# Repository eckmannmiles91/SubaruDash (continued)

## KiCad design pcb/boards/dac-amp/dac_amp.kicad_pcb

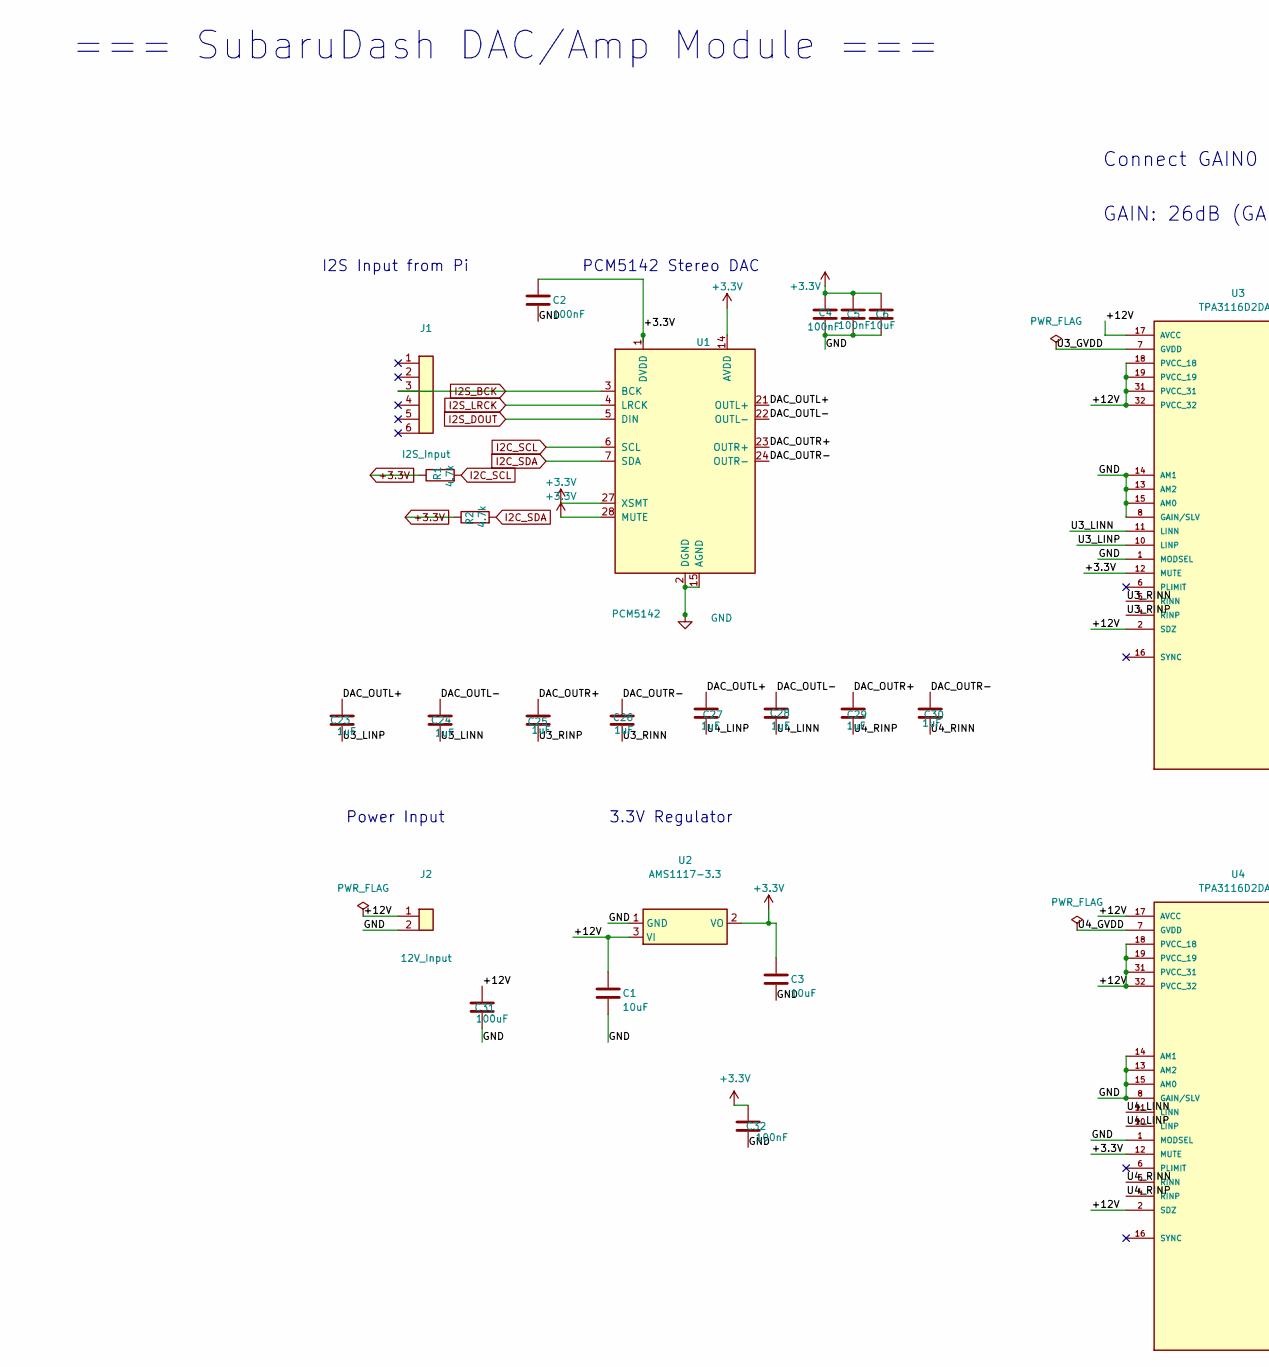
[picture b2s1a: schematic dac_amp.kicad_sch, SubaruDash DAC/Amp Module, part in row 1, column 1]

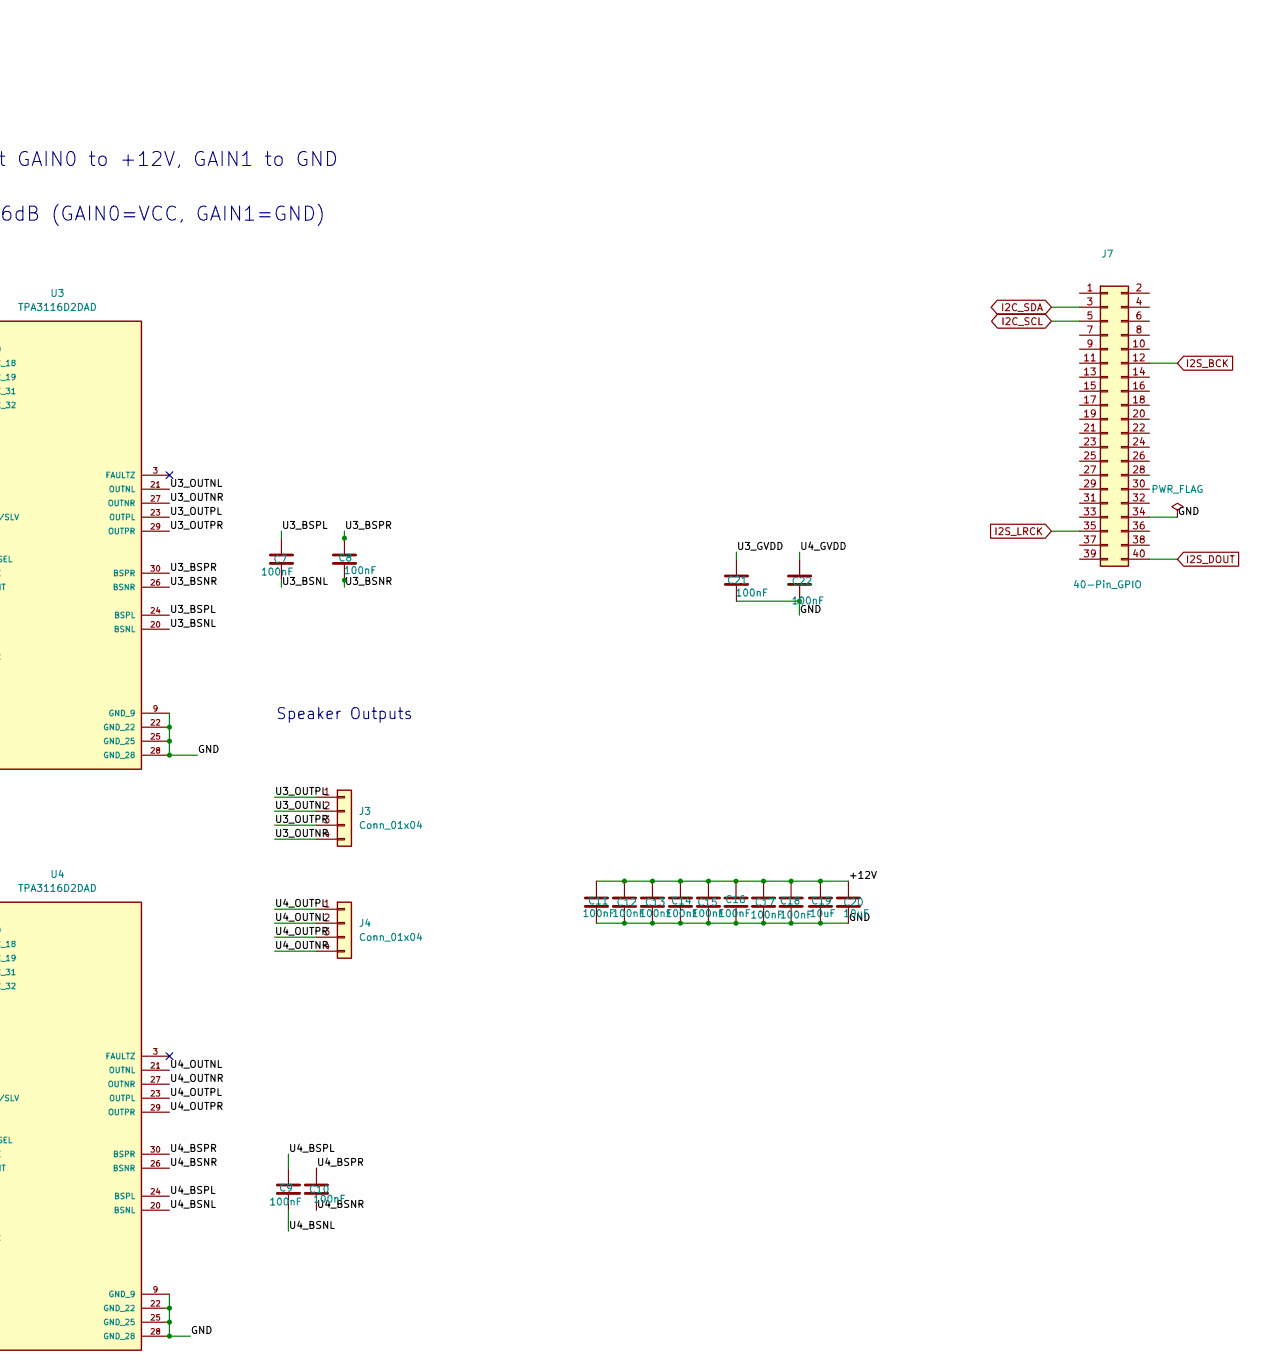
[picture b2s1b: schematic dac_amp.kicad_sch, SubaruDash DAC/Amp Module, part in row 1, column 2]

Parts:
C1, C3, C6: 10uF; C_0805_2012Metric
C2, C4, C5, C7, C8, C9, C10, C11, C12, C13, C14, C15, C16, C17, C18, C21, C22, C32: 100nF; C_0805_2012Metric
C19, C20: 10uF; C_1206_3216Metric
C23, C24, C25, C26, C27, C28, C29, C30: 1uF; C_0805_2012Metric
C31: 100uF; CP_Radial_D8.0mm_P3.50mm
J1: I2S_Input; PinHeader_1x06_P2.54mm_Vertical
J2: 12V_Input; PhoenixContact_MSTBA_2,5_2-G-5,08_1x02_P5.08mm_Horizontal
J3, J4: Conn_01x04; TerminalBlock_Phoenix_PT-1,5-4-3.5-H_1x04_P3.50mm_Horizontal
J7: 40-Pin_GPIO; PinSocket_2x20_P2.54mm_Vertical
R1, R2: 4.7k; R_0805_2012Metric
U1: PCM5142; TQFP-32_7x7mm_P0.8mm
U2: AMS1117-3.3; SOT-223-3_TabPin2
U3, U4: TPA3116D2DAD; Texas_DAD0032A_HTSSOP-32_6.1x11mm_P0.65mm_TopEP3.71x3.81mm; PARTREV G; DigiKey_Part_Number 296-30433-5-ND

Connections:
+3.3V: C2.1, C3.1, C4.1, C5.1, C6.1, C32.1, R1.1, R2.1, U1.1 (DVDD), U1.14 (AVDD), U1.27 (XSMT), U1.28 (MUTE), U2.2 (VO), U3.12 (MUTE), U4.12 (MUTE)
/+12V: C1.1, C11.1, C12.1, C13.1, C14.1, C15.1, C16.1, C17.1, C18.1, C19.1, C20.1, C31.1, J2.1, U2.3 (VI), U3.2 (SDZ), U3.17 (AVCC), U3.18 (PVCC_18), U3.19 (PVCC_19), U3.31 (PVCC_31), U3.32 (PVCC_32), U4.2 (SDZ), U4.17 (AVCC), U4.18 (PVCC_18), U4.19 (PVCC_19), U4.31 (PVCC_31), U4.32 (PVCC_32)
/DAC_OUTL+: C23.1, C27.1, U1.21 (OUTL+)
/DAC_OUTL-: C24.1, C28.1, U1.22 (OUTL-)
/DAC_OUTR+: C25.1, C29.1, U1.23 (OUTR+)
/DAC_OUTR-: C26.1, C30.1, U1.24 (OUTR-)
/U3_BSNL: C7.2, U3.20 (BSNL)
/U3_BSNR: C8.2, U3.26 (BSNR)
/U3_BSPL: C7.1, U3.24 (BSPL)
/U3_BSPR: C8.1, U3.30 (BSPR)
/U3_GVDD: C21.1, U3.7 (GVDD)
/U3_LINN: C24.2, U3.11 (LINN)
/U3_LINP: C23.2, U3.10 (LINP)
/U3_OUTNL: J3.2, U3.21 (OUTNL)
/U3_OUTNR: J3.4, U3.27 (OUTNR)
/U3_OUTPL: J3.1, U3.23 (OUTPL)
/U3_OUTPR: J3.3, U3.29 (OUTPR)
/U3_RINN: C26.2, U3.5 (RINN)
/U3_RINP: C25.2, U3.4 (RINP)
/U4_BSNL: C9.2, U4.20 (BSNL)
/U4_BSNR: C10.2, U4.26 (BSNR)
/U4_BSPL: C9.1, U4.24 (BSPL)
/U4_BSPR: C10.1, U4.30 (BSPR)
/U4_GVDD: C22.1, U4.7 (GVDD)
/U4_LINN: C28.2, U4.11 (LINN)
/U4_LINP: C27.2, U4.10 (LINP)
/U4_OUTNL: J4.2, U4.21 (OUTNL)
/U4_OUTNR: J4.4, U4.27 (OUTNR)
/U4_OUTPL: J4.1, U4.23 (OUTPL)
/U4_OUTPR: J4.3, U4.29 (OUTPR)
/U4_RINN: C30.2, U4.5 (RINN)
/U4_RINP: C29.2, U4.4 (RINP)
GND: C1.2, C2.2, C3.2, C4.2, C5.2, C6.2, C11.2, C12.2, C13.2, C14.2, C15.2, C16.2, C17.2, C18.2, C19.2, C20.2, C21.2, C22.2, C31.2, C32.2, J2.2, J7.34, U1.2 (DGND), U1.15 (AGND), U2.1 (GND), U3.1 (MODSEL), U3.8 (GAIN/SLV), U3.9 (GND_9), U3.13 (AM2), U3.14 (AM1), U3.15 (AM0), U3.22 (GND_22), U3.25 (GND_25), U3.28 (GND_28), U4.1 (MODSEL), U4.8 (GAIN/SLV), U4.9 (GND_9), U4.13 (AM2), U4.14 (AM1), U4.15 (AM0), U4.22 (GND_22), U4.25 (GND_25), U4.28 (GND_28)
I2C_SCL: J7.5, R1.2, U1.6 (SCL)
I2C_SDA: J7.3, R2.2, U1.7 (SDA)
I2S_BCK: J1.3, J7.12, U1.3 (BCK)
I2S_DOUT: J7.40, U1.5 (DIN)
I2S_LRCK: J7.35, U1.4 (LRCK)

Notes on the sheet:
=== SubaruDash DAC/Amp Module ===
3.3V Regulator
I2S Input from Pi
GAIN: 26dB (GAIN0=VCC, GAIN1=GND)
PCM5142 Stereo DAC
Speaker Outputs
Power Input
Connect GAIN0 to +12V, GAIN1 to GND

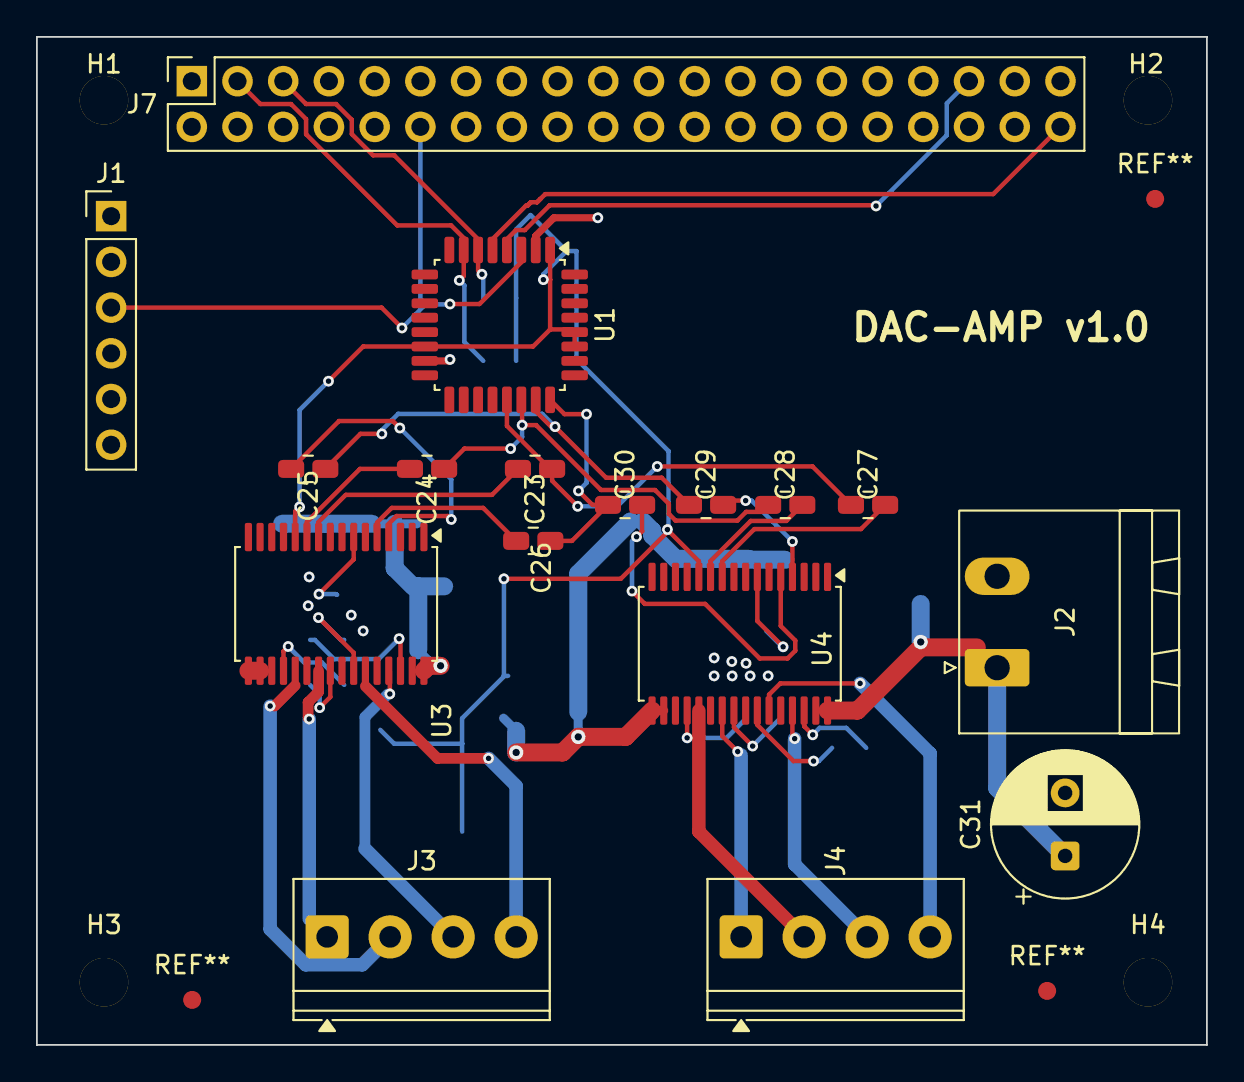
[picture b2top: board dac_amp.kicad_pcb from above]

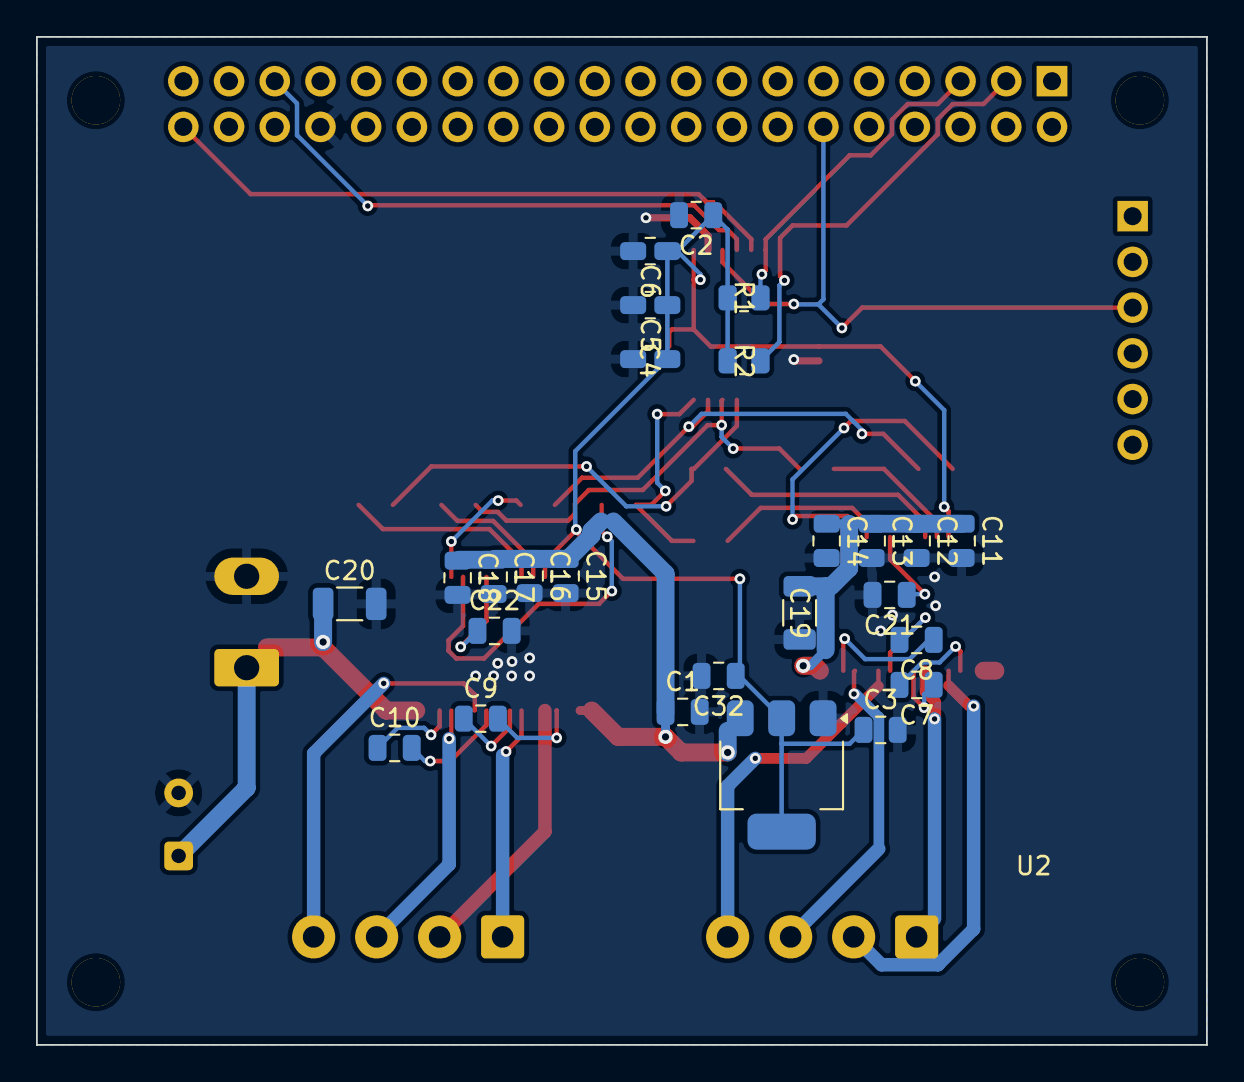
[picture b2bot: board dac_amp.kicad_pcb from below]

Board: 2 copper layers, 65.0 x 56.0 mm, 47 parts (12 on the bottom side), 38 nets.

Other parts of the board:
H1, H2, H3, H4: MountingHole; MountingHole_2.7mm_M2.5

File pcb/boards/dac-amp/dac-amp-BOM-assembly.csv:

Designator,Quantity,Value,Footprint,MPN,Manufacturer,Description
U1,1,PCM5142,TQFP-32_7x7mm_P0.8mm,PCM5142PW,Texas Instruments,32-bit Stereo I2S DAC
U2,1,AMS1117-3.3,SOT-223-3_TabPin2,AMS1117-3.3,Advanced Monolithic Systems,3.3V LDO Regulator
U3,1,TPA3116D2,HTSSOP-32-1EP_6.1x11mm_P0.65mm,TPA3116D2DADR,Texas Instruments,50W Class-D Stereo Amplifier
U4,1,TPA3116D2,HTSSOP-32-1EP_6.1x11mm_P0.65mm,TPA3116D2DADR,Texas Instruments,50W Class-D Stereo Amplifier
C1,1,10uF,C_0805_2012Metric,CL21A106KOQNNNE,Samsung,10uF 16V X5R 0805
C3,1,10uF,C_0805_2012Metric,CL21A106KOQNNNE,Samsung,10uF 16V X5R 0805
C2,1,100nF,C_0805_2012Metric,CL21B104KBCNNNC,Samsung,100nF 50V X7R 0805
J1,1,I2S_Input,PinHeader_1x06_P2.54mm_Vertical,PH1-06-UA,Adam Tech,1x6 Pin Header 2.54mm
J2,1,12V_Input,PhoenixContact_MSTBA_2.5_2-G-5.08,1757019,Phoenix Contact,2-pos Terminal Block 5.08mm
J3,1,Front_Left,PhoenixContact_MSTBA_2.5_2-G-5.08,1757019,Phoenix Contact,2-pos Terminal Block 5.08mm
J4,1,Front_Right,PhoenixContact_MSTBA_2.5_2-G-5.08,1757019,Phoenix Contact,2-pos Terminal Block 5.08mm
J5,1,Rear_Left,PhoenixContact_MSTBA_2.5_2-G-5.08,1757019,Phoenix Contact,2-pos Terminal Block 5.08mm
J6,1,Rear_Right,PhoenixContact_MSTBA_2.5_2-G-5.08,1757019,Phoenix Contact,2-pos Terminal Block 5.08mm
J7,1,40-Pin_GPIO,PinSocket_2x20_P2.54mm_Vertical,PPPC202LFBN-RC,Sullins,2x20 Pin Socket 2.54mm

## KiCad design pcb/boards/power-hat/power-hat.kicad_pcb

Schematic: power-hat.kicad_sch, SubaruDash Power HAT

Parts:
C1, C5, C6: 100nF; C_0805_2012Metric
C2: 10uF; C_1206_3216Metric
C3, C4, C10, C11: 22pF; C_0805_2012Metric
C7: 2.2uF; C_0805_2012Metric
C8: 47pF; C_1206_3216Metric
C9: 22uF; C_1206_3216Metric
C_BOOT1: 100nF; C_0805_2012Metric
C_COMP1: 2.2nF; C_0805_2012Metric
D1: SMBJ18A; D_SMB
D2: SS34; D_SMA
F1: 5A; Fuseholder_Blade_Mini_Keystone_3568
J1: Micro-Fit_3.0; Molex_Micro-Fit_3.0_43045-0612_2x03_P3.00mm_Vertical
J2: Raspberry_Pi_GPIO; PinHeader_2x20_P2.54mm_Vertical
J3: ISP; PinHeader_2x03_P2.54mm_Vertical
J4: FAN_4PIN; PinHeader_1x04_P2.54mm_Vertical
JP1: Jumper; PinHeader_1x02_P2.54mm_Vertical
JP2: 5V/12V; PinHeader_1x03_P2.54mm_Vertical
L1: 33uH; L_Bourns_SRN6045TA
Q1: IRLB8721PBF; TO-220-3_Vertical
Q2, Q3: 2N7002; SOT-23
R1: 10k 1%; R_0805_2012Metric
R2: 470; R_0805_2012Metric
R3: 51k 1%; R_0805_2012Metric
R4, R5, R8: 10k; R_0805_2012Metric
R6, R9, R10: 1k; R_0805_2012Metric
R7: 120; R_0805_2012Metric
R_COMP1: 10k; R_0805_2012Metric
R_RT1: 100k; R_0805_2012Metric
U1: TPS54560BDDA; Texas_R-PDSO-G8_EP2.95x4.9mm_Mask2.4x3.1mm_ThermalVias
U2: LTV-817S; DIP-4_W7.62mm
U3: attiny85; DIP-8_W7.62mm
Y1: 16Mhz Crystal; Crystal_HC49-4H_Vertical

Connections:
12V_ACC: J1.3, R4.1
12V_FUSED: C9.1, D1.1 (A1), D2.1 (K), F1.2, J2.1, U1.2 (VIN)
12V_IGN: D2.2 (A), F1.1, J1.1, J1.2, R6.1, U1.3 (EN)
12V_SWITCHED: Q1.2 (D), Q1.3 (S)
+3.3V: C1.1, C4.1, C5.1, C6.1, J2.17, R7.1, R8.1, U3.8 (VCC)
+5V: C2.1, C8.1, J2.2, J2.4, L1.2, R3.1
/COMP_RC: C_COMP1.1, R_COMP1.2
/Q1_GATE: Q1.1 (G), R2.1, R5.1
/RT_CLK: R_RT1.1, U1.4 (RT/CLK)
/U1_BOOT: C_BOOT1.2, U1.1 (BOOT)
/U1_COMP: R_COMP1.1, U1.6 (COMP)
/U1_FB: R1.2, R3.2, U1.5 (FB)
/U1_SW: C_BOOT1.1, L1.1, U1.8 (SW)
FAN+: J4.2
FAN-: Q3.3 (D)
FAN_PWM: J2.32, J4.4, Q3.1 (G), R10.1
FAN_TACH: J2.33, J4.3
GATE_CTRL: Q2.1 (G), R2.2, R5.2, R8.2, R9.1, U3.2 (XTAL1/PB3)
GND: C1.2, C2.2, C3.2, C4.2, C5.2, C6.2, C7.2, C9.2, C10.2, C11.2, C_COMP1.2, D1.2 (A2), J1.4, J1.5, J1.6, J2.6, J2.9, J2.14, J2.20, J2.25, J2.30, J2.34, J2.39, J4.1, Q2.2 (S), Q2.3 (D), Q3.2 (S), R1.1, R6.2, R10.2, R_RT1.2, U1.7 (GND), U1.9 (GND), U2.1, U2.2, U2.3, U3.4 (GND)
HEARTBEAT_LED: U3.5 (AREF/PB0)
IGN_DETECT: C3.1, U2.4, U3.7 (PB2)
Q2_GATE: R9.2
R6_OUT: R4.2
RESET: R7.2, U3.1 (~RESET/PB5)
SHUTDOWN_REQ: J2.15, U3.3 (XTAL2/PB4)
TIMER_LED: U3.6 (PB1)
U1-FB: C8.2
XTAL1: C7.1, C10.1, Y1.1
XTAL2: C11.1, Y1.2

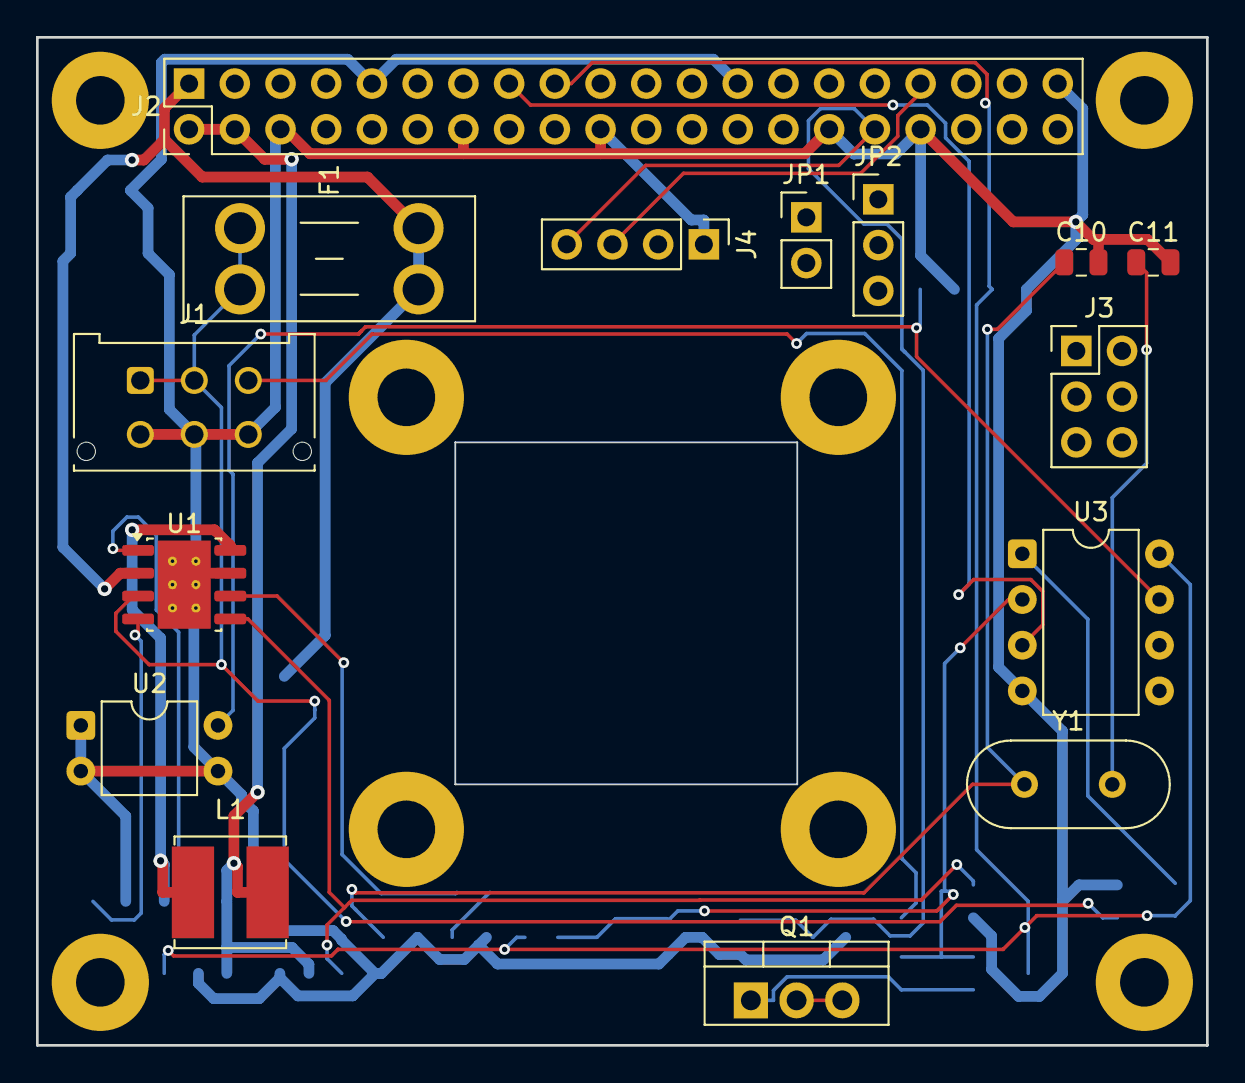
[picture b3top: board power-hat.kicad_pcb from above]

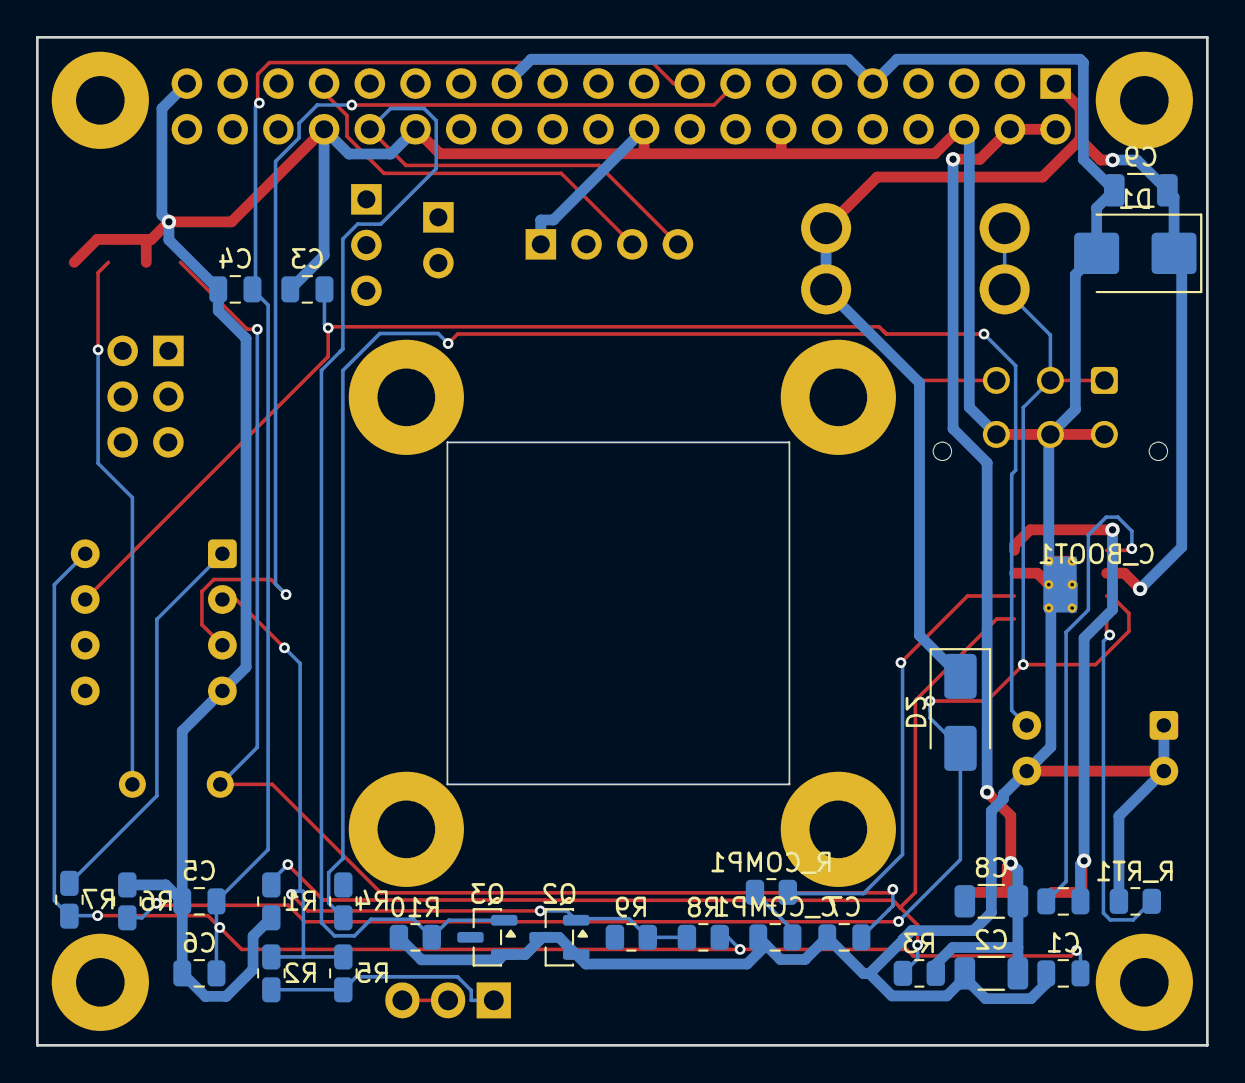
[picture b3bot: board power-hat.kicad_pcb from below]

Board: 2 copper layers, 65.0 x 56.0 mm, 50 parts (27 on the bottom side), 22 nets.

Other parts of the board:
FH1, FH2, FH3, FH4: FanMount; MountingHole_3.2mm_M3
H1, H2, H3, H4: MountingHole; MountingHole_2.7mm_M2.5

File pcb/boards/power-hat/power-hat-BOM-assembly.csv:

Designator,Quantity,Value,Footprint,MPN,Manufacturer,Description
U1,1,TPS54560BDDA,Texas_R-PDSO-G8_EP,TPS54560BDDAR,Texas Instruments,60V 5A Step-Down Converter
U2,1,LTV-817S,DIP-4_W7.62mm,LTV-817S,Lite-On,Optocoupler Phototransistor
U3,1,attiny85,DIP-8_W7.62mm,ATTINY85-20PU,Microchip,8-bit AVR Microcontroller
Q1,1,IRLB8721PBF,TO-220-3_Vertical,IRLB8721PBF,Infineon,N-Channel MOSFET 30V 62A
Q2,1,2N7002,SOT-23,2N7002,ON Semiconductor,N-Channel MOSFET 60V 300mA
Q3,1,2N7002,SOT-23,2N7002,ON Semiconductor,N-Channel MOSFET 60V 300mA
D1,1,SMBJ18A,D_SMB,SMBJ18A,Littelfuse,TVS Diode 18V SMB
D2,1,SS34,D_SMA,SS34,ON Semiconductor,Schottky Diode 40V 3A SMA
L1,1,33uH,L_Bourns_SRN6045TA,SRN6045TA-330M,Bourns,33uH 3A Power Inductor
Y1,1,16MHz Crystal,Crystal_HC49-4H_Vertical,FOXSLF/160-20,FOX Electronics,16MHz Crystal HC49
F1,1,5A,Fuseholder_Blade_Mini_Keystone_3568,3568,Keystone,Mini Blade Fuse Holder
C1,1,100nF,C_0805_2012Metric,CL21B104KBCNNNC,Samsung,100nF 50V X7R 0805
C5,1,100nF,C_0805_2012Metric,CL21B104KBCNNNC,Samsung,100nF 50V X7R 0805
C6,1,100nF,C_0805_2012Metric,CL21B104KBCNNNC,Samsung,100nF 50V X7R 0805
C_BOOT1,1,100nF,C_0805_2012Metric,CL21B104KBCNNNC,Samsung,100nF 50V X7R 0805
C3,1,22pF,C_0805_2012Metric,CL21C220JBANNNC,Samsung,22pF 50V C0G 0805
C4,1,22pF,C_0805_2012Metric,CL21C220JBANNNC,Samsung,22pF 50V C0G 0805
C10,1,22pF,C_0805_2012Metric,CL21C220JBANNNC,Samsung,22pF 50V C0G 0805
C11,1,22pF,C_0805_2012Metric,CL21C220JBANNNC,Samsung,22pF 50V C0G 0805
C7,1,2.2uF,C_0805_2012Metric,CL21B225KOFNNNE,Samsung,2.2uF 16V X7R 0805
C_COMP1,1,2.2nF,C_0805_2012Metric,CL21B222KBANNNC,Samsung,2.2nF 50V X7R 0805
C8,1,47pF,C_1206_3216Metric,CL31C470JBCNNNC,Samsung,47pF 50V C0G 1206
C2,1,10uF,C_1206_3216Metric,CL31B106KAHNNNE,Samsung,10uF 25V X5R 1206
C9,1,22uF,C_1206_3216Metric,CL31A226KAHNNNE,Samsung,22uF 25V X5R 1206
R1,1,10k 1%,R_0805_2012Metric,RC0805FR-0710KL,Yageo,10k 1% 0805
R2,1,470,R_0805_2012Metric,RC0805FR-07470RL,Yageo,470 ohm 1% 0805
R3,1,51k 1%,R_0805_2012Metric,RC0805FR-0751KL,Yageo,51k 1% 0805
R4,1,10k,R_0805_2012Metric,RC0805FR-0710KL,Yageo,10k 1% 0805
R5,1,10k,R_0805_2012Metric,RC0805FR-0710KL,Yageo,10k 1% 0805
R6,1,1k,R_0805_2012Metric,RC0805FR-071KL,Yageo,1k 1% 0805
R7,1,120,R_0805_2012Metric,RC0805FR-07120RL,Yageo,120 ohm 1% 0805
R8,1,10k,R_0805_2012Metric,RC0805FR-0710KL,Yageo,10k 1% 0805
R9,1,1k,R_0805_2012Metric,RC0805FR-071KL,Yageo,1k 1% 0805
R10,1,1k,R_0805_2012Metric,RC0805FR-071KL,Yageo,1k 1% 0805
R_COMP1,1,10k,R_0805_2012Metric,RC0805FR-0710KL,Yageo,10k 1% 0805
R_RT1,1,100k,R_0805_2012Metric,RC0805FR-07100KL,Yageo,100k 1% 0805
J1,1,Micro-Fit_3.0,Molex_Micro-Fit_3.0_43045-0612,43045-0612,Molex,2x3 Micro-Fit 3.0mm
J2,1,Raspberry_Pi_GPIO,PinHeader_2x20_P2.54mm_Vertical,PH2-40-UA,Adam Tech,2x20 Pin Header 2.54mm
J3,1,ISP,PinHeader_2x03_P2.54mm_Vertical,PH2-06-UA,Adam Tech,2x3 Pin Header 2.54mm
J4,1,FAN_4PIN,PinHeader_1x04_P2.54mm_Vertical,PH1-04-UA,Adam Tech,1x4 Pin Header 2.54mm
JP1,1,Jumper,PinHeader_1x02_P2.54mm_Vertical,PH1-02-UA,Adam Tech,1x2 Pin Header 2.54mm
JP2,1,5V/12V,PinHeader_1x03_P2.54mm_Vertical,PH1-03-UA,Adam Tech,1x3 Pin Header 2.54mm

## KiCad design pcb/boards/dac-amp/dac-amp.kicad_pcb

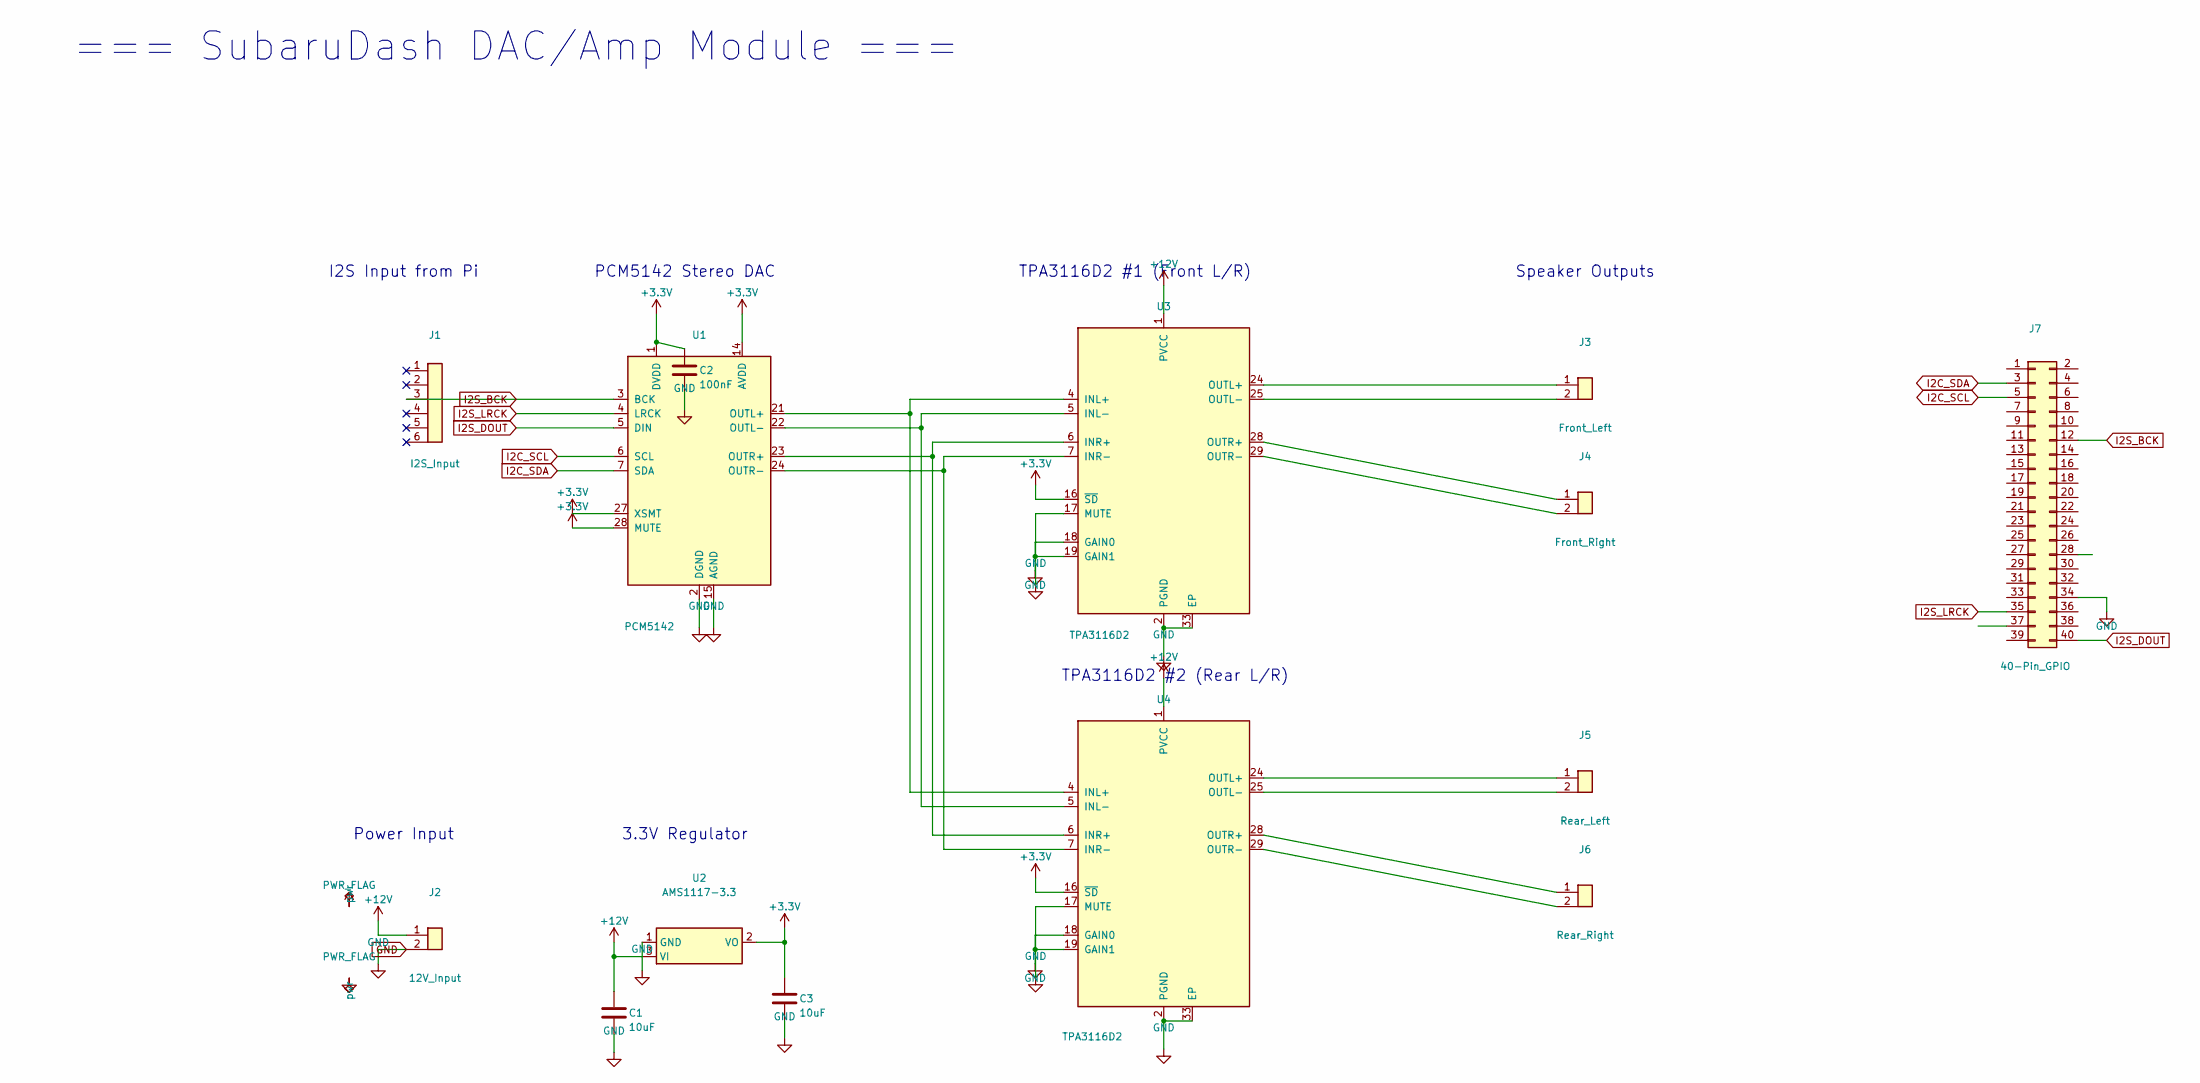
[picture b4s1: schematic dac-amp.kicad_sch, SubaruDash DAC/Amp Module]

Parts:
C1, C3: 10uF; C_0805_2012Metric
C2: 100nF; C_0805_2012Metric
J1: I2S_Input; PinHeader_1x06_P2.54mm_Vertical
J2: 12V_Input; PhoenixContact_MSTBA_2,5_2-G-5,08_1x02_P5.08mm_Horizontal
J3: Front_Left; PhoenixContact_MSTBA_2,5_2-G-5,08_1x02_P5.08mm_Horizontal
J4: Front_Right; PhoenixContact_MSTBA_2,5_2-G-5,08_1x02_P5.08mm_Horizontal
J5: Rear_Left; PhoenixContact_MSTBA_2,5_2-G-5,08_1x02_P5.08mm_Horizontal
J6: Rear_Right; PhoenixContact_MSTBA_2,5_2-G-5,08_1x02_P5.08mm_Horizontal
J7: 40-Pin_GPIO; PinSocket_2x20_P2.54mm_Vertical
U1: PCM5142; TQFP-32_7x7mm_P0.8mm
U2: AMS1117-3.3; SOT-223-3_TabPin2
U3, U4: TPA3116D2; HTSSOP-32-1EP_6.1x11mm_P0.65mm_EP5.2x11mm_Mask4.11x4.36mm_T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

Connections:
+3.3V: C2.1, C3.1, U1.1 (DVDD), U1.14 (AVDD), U1.27 (XSMT), U1.28 (MUTE), U2.2 (VO), U3.16 (~SD), U4.16 (~SD)
+12V: C1.1, J2.1, U2.3 (VI), U3.1 (PVCC), U4.1 (PVCC)
GND: C1.2, C2.2, C3.2, J2.2, J7.34, U1.2 (DGND), U1.15 (AGND), U2.1 (GND), U3.2 (PGND), U3.17 (MUTE), U3.18 (GAIN0), U3.19 (GAIN1), U3.33 (EP), U4.2 (PGND), U4.17 (MUTE), U4.18 (GAIN0), U4.19 (GAIN1), U4.33 (EP)
I2C_SCL: J7.5, U1.6 (SCL)
I2C_SDA: J7.3, U1.7 (SDA)
I2S_BCK: J1.3, J7.12, U1.3 (BCK)
I2S_DOUT: J7.40, U1.5 (DIN)
I2S_LRCK: J7.35, U1.4 (LRCK)
unnamed: J3.1, U3.24 (OUTL+)
unnamed: J3.2, U3.25 (OUTL-)
unnamed: J4.1, U3.28 (OUTR+)
unnamed: J4.2, U3.29 (OUTR-)
unnamed: J5.1, U4.24 (OUTL+)
unnamed: J5.2, U4.25 (OUTL-)
unnamed: J6.1, U4.28 (OUTR+)
unnamed: J6.2, U4.29 (OUTR-)
unnamed: U1.21 (OUTL+), U3.4 (INL+), U4.4 (INL+)
unnamed: U1.22 (OUTL-), U3.5 (INL-), U4.5 (INL-)
unnamed: U1.23 (OUTR+), U3.6 (INR+), U4.6 (INR+)
unnamed: U1.24 (OUTR-), U3.7 (INR-), U4.7 (INR-)

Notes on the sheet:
TPA3116D2 #1 (Front L/R)
=== SubaruDash DAC/Amp Module ===
3.3V Regulator
I2S Input from Pi
TPA3116D2 #2 (Rear L/R)
PCM5142 Stereo DAC
Speaker Outputs
Power Input

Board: 2 copper layers, 18 parts (4 on the bottom side), 20 nets, no tracks yet.

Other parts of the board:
H1, H2, H3, H4: MountingHole; MountingHole_2.7mm_M2.5

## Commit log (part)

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2026-02-02 Add custom PCB design document to README
